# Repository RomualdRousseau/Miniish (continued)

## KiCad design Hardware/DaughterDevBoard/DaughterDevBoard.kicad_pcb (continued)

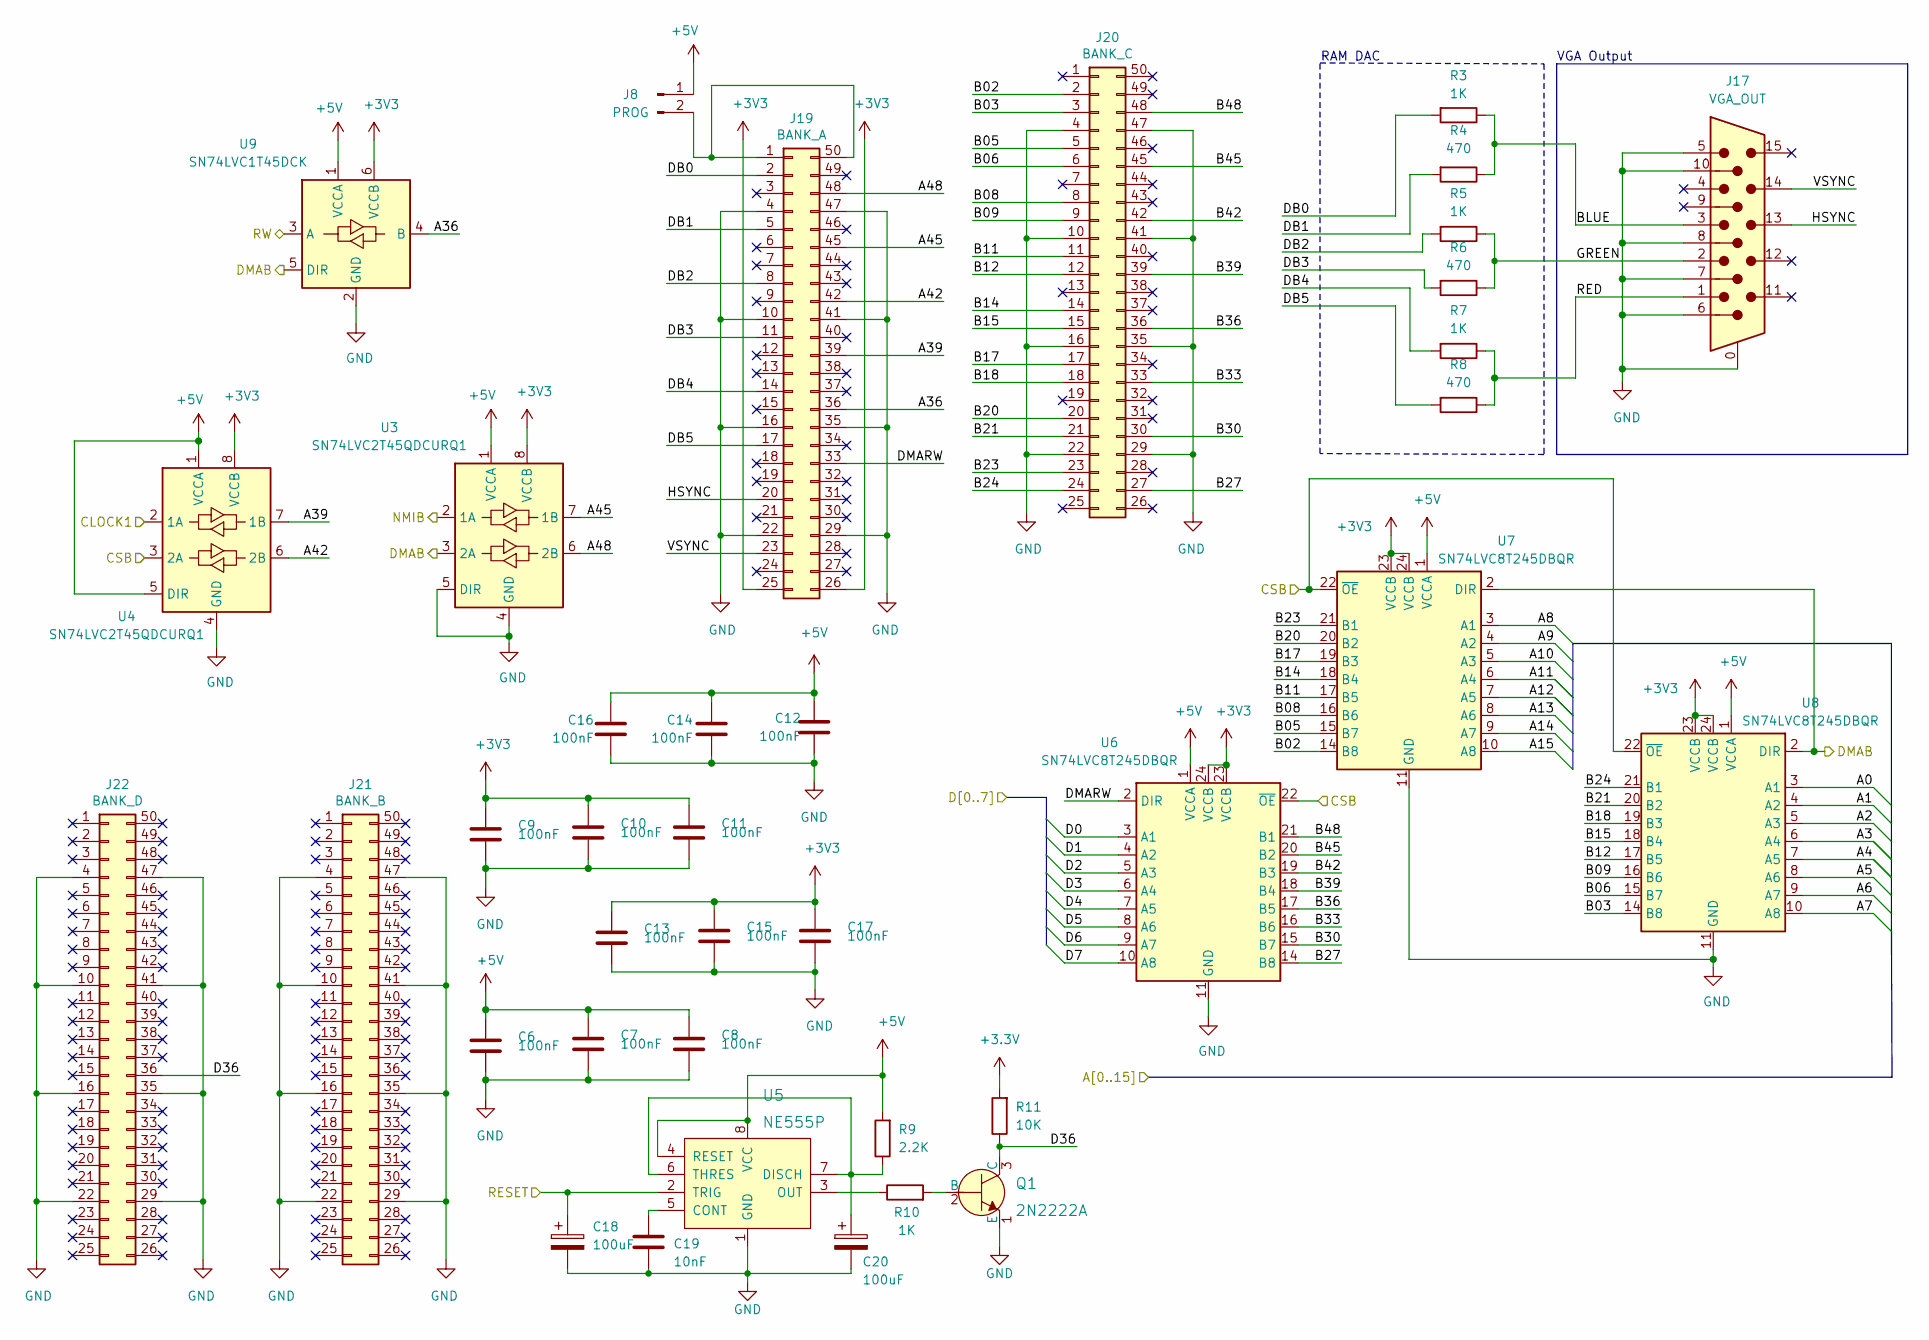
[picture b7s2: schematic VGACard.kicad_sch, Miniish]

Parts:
C6, C7, C8, C9, C10, C11, C12, C13, C14, C15, C16, C17: 100nF; C_0603_1608Metric
C18, C20: 100uF; CP_Radial_D5.0mm_P2.50mm
C19: 10nF; C_Disc_D5.0mm_W2.5mm_P2.50mm
J8: PROG; PinHeader_1x02_P2.54mm_Vertical
J17: VGA_OUT; DSUB-15-HD_Female_Horizontal_P2.29x1.98mm_EdgePinOffset8.35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
J19: BANK_A; 4UCON_2x25_P0.50mm_Vertical
J20: BANK_C; 4UCON_2x25_P0.50mm_Vertical
J21: BANK_B; 4UCON_2x25_P0.50mm_Vertical
J22: BANK_D; 4UCON_2x25_P0.50mm_Vertical
Q1: 2N2222A; TO-18-3; MPN 2N2222A; Digi-Key_PN 2N2222ACS-ND
R3, R5, R7, R10: 1K; R_Axial_DIN0207_L6.3mm_D2.5mm_P10.16mm_Horizontal
R4, R6, R8: 470; R_Axial_DIN0207_L6.3mm_D2.5mm_P10.16mm_Horizontal
R9: 2.2K; R_Axial_DIN0207_L6.3mm_D2.5mm_P10.16mm_Horizontal
R11: 10K; R_Axial_DIN0207_L6.3mm_D2.5mm_P10.16mm_Horizontal
U3, U4: SN74LVC2T45QDCURQ1; VSSOP-8_2.3x2mm_P0.5mm
U5: NE555P; DIP-8_W7.62mm; MPN NE555P; Digi-Key_PN 296-1411-5-ND
U6, U7, U8: SN74LVC8T245DBQR; TSSOP-24_4.4x7.8mm_P0.65mm
U9: SN74LVC1T45DCK; SOT-363_SC-70-6

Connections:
+5V: C6.1, C7.1, C8.1, C12.2, C14.2, C16.2, J8.1, R9.2, U3.1 (VCCA), U4.1 (VCCA), U4.5 (DIR), U5.4 (RESET), U5.8 (VCC), U6.1 (VCCA), U7.1 (VCCA), U8.1 (VCCA), U9.1 (VCCA); also elsewhere on the board
/AB0: U8.3 (A1); also elsewhere on the board
/AB1: U8.4 (A2); also elsewhere on the board
/AB2: U8.5 (A3); also elsewhere on the board
/AB3: U8.6 (A4); also elsewhere on the board
/AB4: U8.7 (A5); also elsewhere on the board
/AB5: U8.8 (A6); also elsewhere on the board
/AB6: U8.9 (A7); also elsewhere on the board
/AB7: U8.10 (A8); also elsewhere on the board
/AB8: U7.3 (A1); also elsewhere on the board
/AB9: U7.4 (A2); also elsewhere on the board
/AB10: U7.5 (A3); also elsewhere on the board
/AB11: U7.6 (A4); also elsewhere on the board
/AB12: U7.7 (A5); also elsewhere on the board
/AB13: U7.8 (A6); also elsewhere on the board
/AB14: U7.9 (A7); also elsewhere on the board
/AB15: U7.10 (A8); also elsewhere on the board
/DB0: U6.3 (A1); also elsewhere on the board
/DB1: U6.4 (A2); also elsewhere on the board
/DB2: U6.5 (A3); also elsewhere on the board
/DB3: U6.6 (A4); also elsewhere on the board
/DB4: U6.7 (A5); also elsewhere on the board
/DB5: U6.8 (A6); also elsewhere on the board
/DB6: U6.9 (A7); also elsewhere on the board
/DB7: U6.10 (A8); also elsewhere on the board
/VGA Card/A36: J19.36, U9.4 (B)
/VGA Card/A39: J19.39, U4.7 (1B)
/VGA Card/A42: J19.42, U4.6 (2B)
/VGA Card/A45: J19.45, U3.7 (1B)
/VGA Card/A48: J19.48, U3.6 (2B)
/VGA Card/B02: J20.2, U7.14 (B8)
/VGA Card/B03: J20.3, U8.14 (B8)
/VGA Card/B05: J20.5, U7.15 (B7)
/VGA Card/B06: J20.6, U8.15 (B7)
/VGA Card/B08: J20.8, U7.16 (B6)
/VGA Card/B09: J20.9, U8.16 (B6)
/VGA Card/B11: J20.11, U7.17 (B5)
/VGA Card/B12: J20.12, U8.17 (B5)
/VGA Card/B14: J20.14, U7.18 (B4)
/VGA Card/B15: J20.15, U8.18 (B4)
/VGA Card/B17: J20.17, U7.19 (B3)
/VGA Card/B18: J20.18, U8.19 (B3)
/VGA Card/B20: J20.20, U7.20 (B2)
/VGA Card/B21: J20.21, U8.20 (B2)
/VGA Card/B23: J20.23, U7.21 (B1)
/VGA Card/B24: J20.24, U8.21 (B1)
/VGA Card/B27: J20.27, U6.14 (B8)
/VGA Card/B30: J20.30, U6.15 (B7)
/VGA Card/B33: J20.33, U6.16 (B6)
/VGA Card/B36: J20.36, U6.17 (B5)
/VGA Card/B39: J20.39, U6.18 (B4)
/VGA Card/B42: J20.42, U6.19 (B3)
/VGA Card/B45: J20.45, U6.20 (B2)
/VGA Card/B48: J20.48, U6.21 (B1)
/VGA Card/BLUE: J17.3, R3.1, R4.1
/VGA Card/CLOCK1: U4.2 (1A); also elsewhere on the board
/VGA Card/CSB: U4.3 (2A), U6.22 (~OE), U7.22 (~OE), U8.22 (~OE); also elsewhere on the board
/VGA Card/D36: J22.36, Q1.3 (C), R11.1
/VGA Card/DB0: J19.2, R3.2
/VGA Card/DB1: J19.5, R4.2
/VGA Card/DB2: J19.8, R5.2
/VGA Card/DB3: J19.11, R6.2
/VGA Card/DB4: J19.14, R7.2
/VGA Card/DB5: J19.17, R8.2
/VGA Card/DMAB: U3.3 (2A), U7.2 (DIR), U8.2 (DIR), U9.5 (DIR); also elsewhere on the board
/VGA Card/DMARW: J19.33, U6.2 (DIR)
/VGA Card/GREEN: J17.2, R5.1, R6.1
/VGA Card/HSYNC: J17.13, J19.20
/VGA Card/NMIB: U3.2 (1A); also elsewhere on the board
/VGA Card/RED: J17.1, R7.1, R8.1
/VGA Card/RESET: C18.1, U5.2 (TRIG); also elsewhere on the board
/VGA Card/RW: U9.3 (A); also elsewhere on the board
/VGA Card/VSYNC: J17.14, J19.23
GND: C6.2, C7.2, C8.2, C9.2, C10.2, C11.2, C12.1, C13.2, C14.1, C15.2, C16.1, C17.2, C18.2, C19.2, C20.2, J17.0, J17.5, J17.6, J17.7, J17.8, J17.10, J19.4, J19.10, J19.16, J19.22, J19.29, J19.35, J19.41, J19.47, J20.4, J20.10, J20.16, J20.22, J20.29, J20.35, J20.41, J20.47, J21.4, J21.10, J21.16, J21.22, J21.29, J21.35, J21.41, J21.47, J22.4, J22.10, J22.16, J22.22, J22.29, J22.35, J22.41, J22.47, Q1.1 (E), U3.4 (GND), U3.5 (DIR), U4.4 (GND), U5.1 (GND), U6.11 (GND), U6.12 (GND), U6.13 (GND), U7.11 (GND), U7.12 (GND), U7.13 (GND), U8.11 (GND), U8.12 (GND), U8.13 (GND), U9.2 (GND); also elsewhere on the board
unnamed: C19.1, U5.5 (CONT)
unnamed: C20.1, R9.1, U5.6 (THRES), U5.7 (DISCH)
unnamed: J8.2, J19.1, J19.50
unnamed: Q1.2 (B), R10.2
unnamed: R10.1, U5.3 (OUT)

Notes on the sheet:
RAM DAC
VGA Output

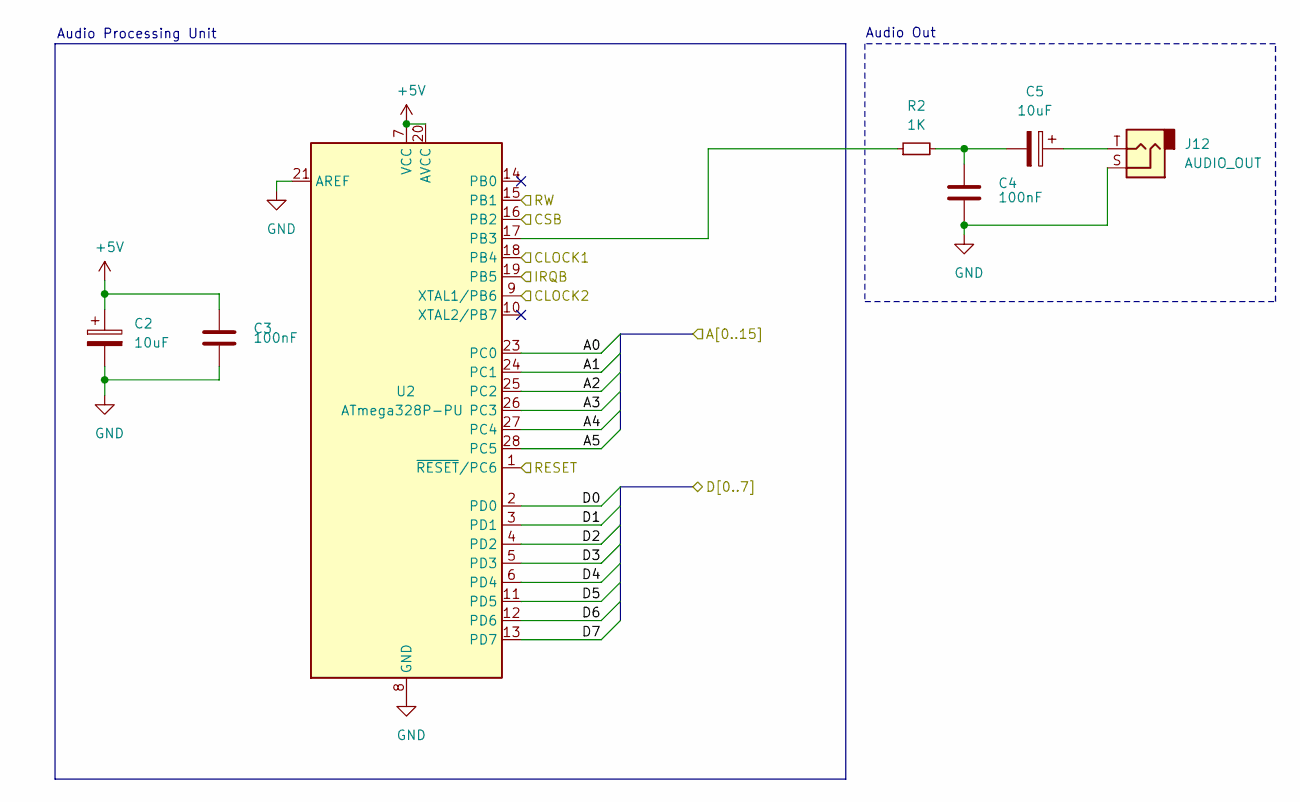
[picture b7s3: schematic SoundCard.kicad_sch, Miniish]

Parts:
C2, C5: 10uF; C_Radial_D5.0mm_H11.0mm_P2.00mm
C3, C4: 100nF; C_Disc_D5.0mm_W2.5mm_P2.50mm
J12: AUDIO_OUT; Jack_3.5mm_CUI_SJ1-3533NG_Horizontal
R2: 1K; R_Axial_DIN0207_L6.3mm_D2.5mm_P10.16mm_Horizontal
U2: ATmega328P-PU; DIP-28_W7.62mm

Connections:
+5V: C2.1, C3.1, U2.7 (VCC), U2.20 (AVCC); also elsewhere on the board
/AA0: U2.23 (PC0); also elsewhere on the board
/AA1: U2.24 (PC1); also elsewhere on the board
/AA2: U2.25 (PC2); also elsewhere on the board
/AA3: U2.26 (PC3); also elsewhere on the board
/AA4: U2.27 (PC4); also elsewhere on the board
/AA5: U2.28 (PC5); also elsewhere on the board
/DA0: U2.2 (PD0); also elsewhere on the board
/DA1: U2.3 (PD1); also elsewhere on the board
/DA2: U2.4 (PD2); also elsewhere on the board
/DA3: U2.5 (PD3); also elsewhere on the board
/DA4: U2.6 (PD4); also elsewhere on the board
/DA5: U2.11 (PD5); also elsewhere on the board
/DA6: U2.12 (PD6); also elsewhere on the board
/DA7: U2.13 (PD7); also elsewhere on the board
/SoundCard/CLOCK1: U2.18 (PB4); also elsewhere on the board
/SoundCard/CSB: U2.16 (PB2); also elsewhere on the board
/SoundCard/IRQB: U2.19 (PB5); also elsewhere on the board
/SoundCard/RESET: U2.1 (~RESET/PC6); also elsewhere on the board
/SoundCard/RW: U2.15 (PB1); also elsewhere on the board
APU_CLOCK: U2.9 (XTAL1/PB6); also elsewhere on the board
GND: C2.2, C3.2, C4.2, J12.S, U2.8 (GND), U2.21 (AREF), U2.22 (GND); also elsewhere on the board
unnamed: C4.1, C5.2, R2.2
unnamed: C5.1, J12.T
unnamed: R2.1, U2.17 (PB3)

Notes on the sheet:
Audio Out
Audio Processing Unit

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
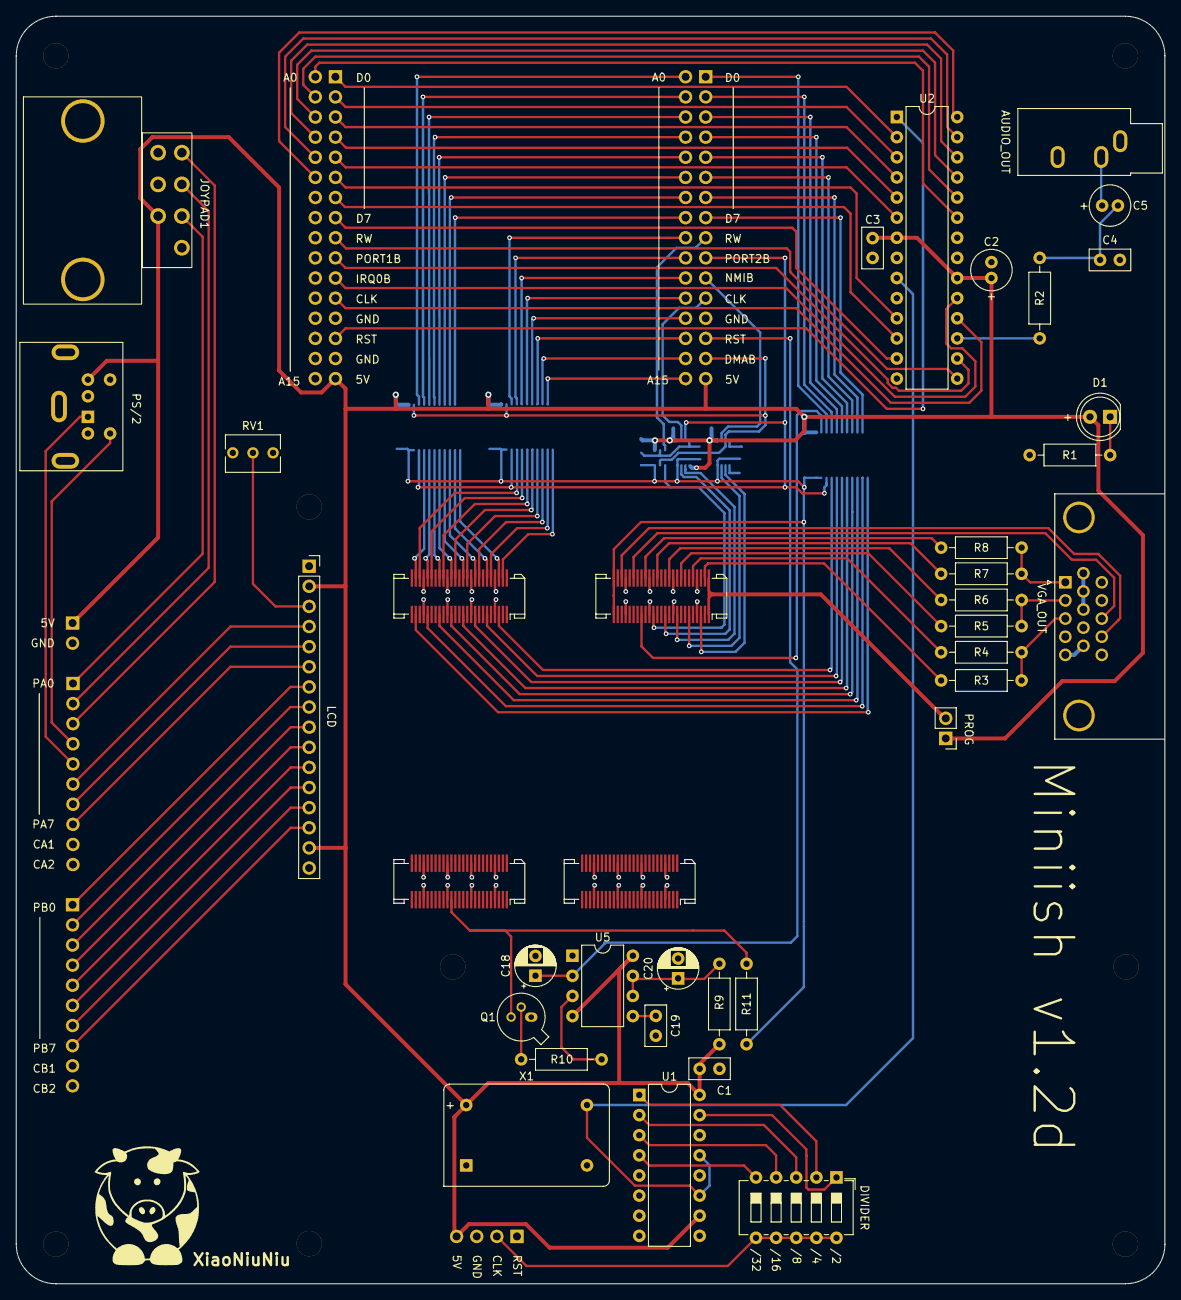
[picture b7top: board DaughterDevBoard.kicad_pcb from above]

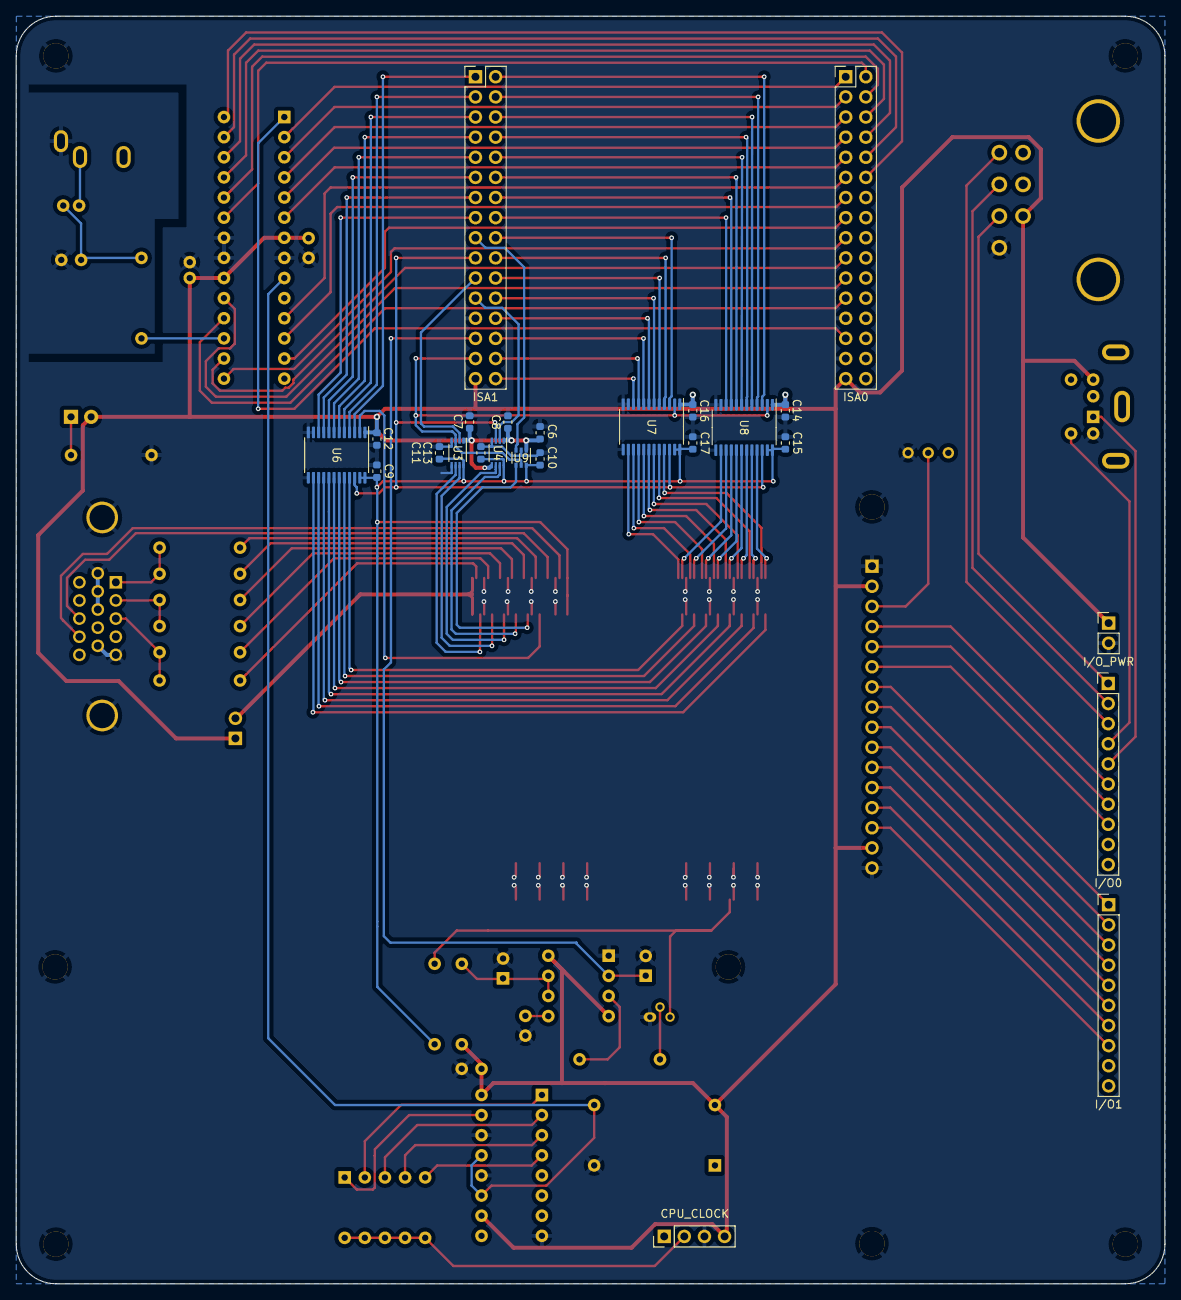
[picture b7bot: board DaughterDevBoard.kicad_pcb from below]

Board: 2 copper layers, 145.0 x 160.0 mm, 70 parts (24 on the bottom side), 127 nets.

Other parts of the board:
H7, H8: MountingHole_Pad
XiaoNiuNiu: LOGO; SmallCow

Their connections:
GND: H7.1, H8.1; also elsewhere on the board

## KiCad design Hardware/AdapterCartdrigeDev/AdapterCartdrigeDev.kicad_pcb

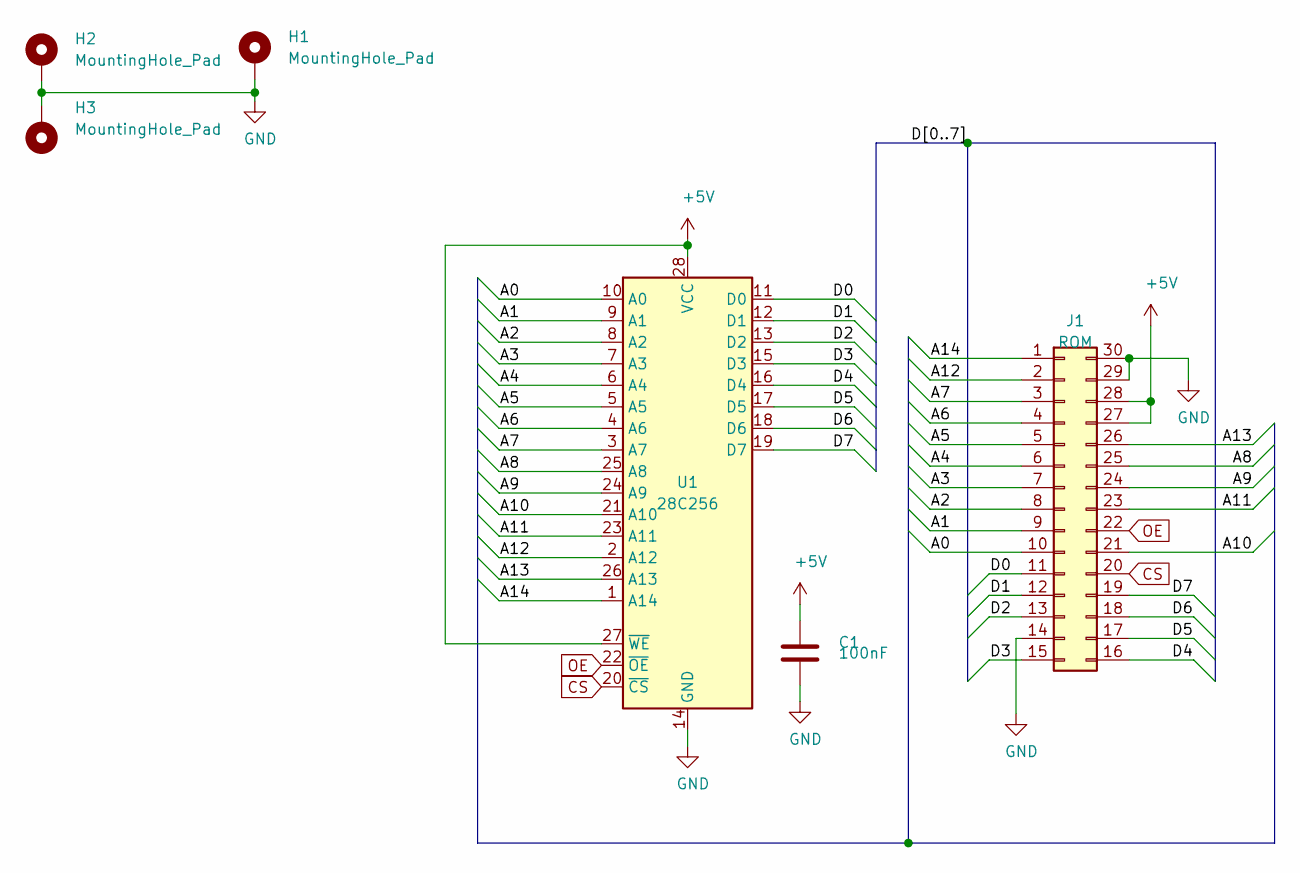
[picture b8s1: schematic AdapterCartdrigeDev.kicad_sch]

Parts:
C1: 100nF; C_Disc_D5.0mm_W2.5mm_P2.50mm
H1, H2, H3: MountingHole_Pad; MountingHole_3.2mm_M3
J1: ROM; PinHeader_2x15_P2.54mm_Vertical
U1: 28C256; DIP_Socket-28_W11.9_W12.7_W15.24_W17.78_W18.5_3M_228-1277-0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

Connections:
+5V: C1.1, J1.27, J1.28, U1.27 (~WE), U1.28 (VCC)
/A0: J1.10, U1.10 (A0)
/A1: J1.9, U1.9 (A1)
/A2: J1.8, U1.8 (A2)
/A3: J1.7, U1.7 (A3)
/A4: J1.6, U1.6 (A4)
/A5: J1.5, U1.5 (A5)
/A6: J1.4, U1.4 (A6)
/A7: J1.3, U1.3 (A7)
/A8: J1.25, U1.25 (A8)
/A9: J1.24, U1.24 (A9)
/A10: J1.21, U1.21 (A10)
/A11: J1.23, U1.23 (A11)
/A12: J1.2, U1.2 (A12)
/A13: J1.26, U1.26 (A13)
/A14: J1.1, U1.1 (A14)
/D0: J1.11, U1.11 (D0)
/D1: J1.12, U1.12 (D1)
/D2: J1.13, U1.13 (D2)
/D3: J1.15, U1.15 (D3)
/D4: J1.16, U1.16 (D4)
/D5: J1.17, U1.17 (D5)
/D6: J1.18, U1.18 (D6)
/D7: J1.19, U1.19 (D7)
CS: J1.20, U1.20 (~CS)
GND: C1.2, H1.1, H2.1, H3.1, J1.14, J1.29, J1.30, U1.14 (GND)
OE: J1.22, U1.22 (~OE)

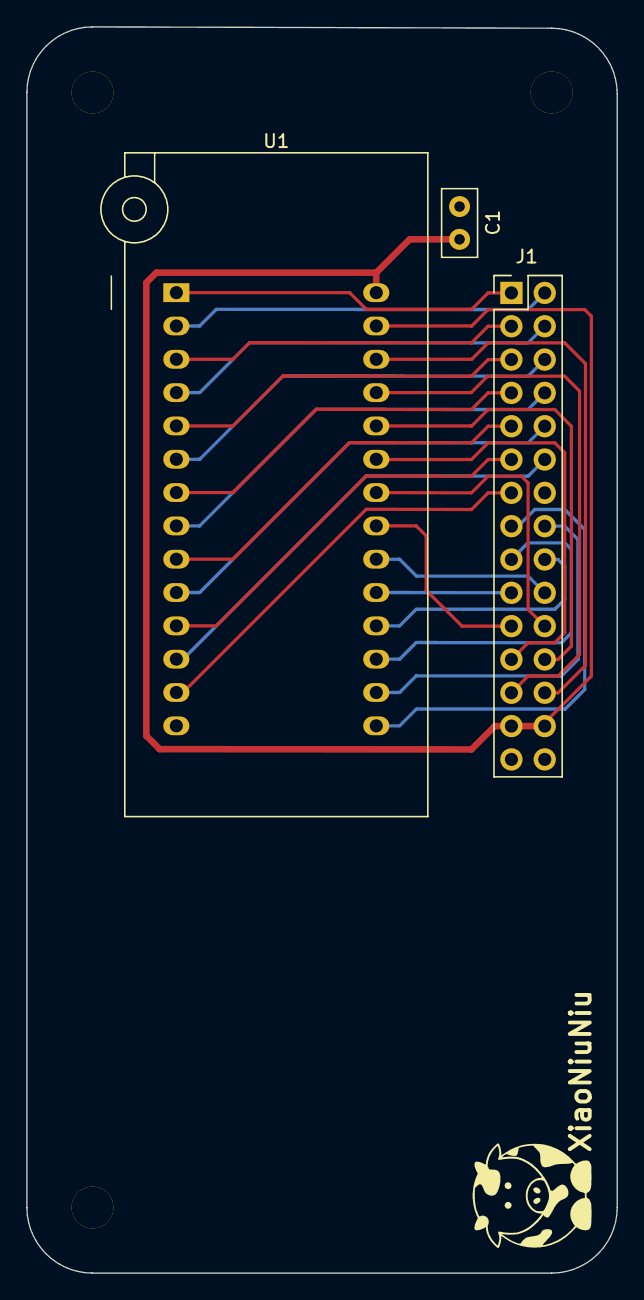
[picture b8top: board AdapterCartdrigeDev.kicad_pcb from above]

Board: 2 copper layers, 45.0 x 95.0 mm, 7 parts (0 on the bottom side), 27 nets.

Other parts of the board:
XiaoNiuNiu: LOGO; VerySmallCow

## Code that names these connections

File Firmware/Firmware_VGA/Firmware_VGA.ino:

/*
    Welcome to VGA v1.0 firmware

    To upload this firmware, select the following board:
    Board: "ATMEGA 328P"
    Clock: "20MHz"
    Bootloader: "Empty"
*/

#define CONTROL_PORT     PORTB
#define VADDR_PORT       PORTC
#define HADDR_PORT       PORTD

#define VADDR7_PIN       0  // PIN 8  (PB0)
#define CTRL_HSYNC_PIN   1  // PIN 9  (PB1)
#define CTRL_VSYNC_PIN   2  // PIN 10 (PB2)
#define CTRL_HLINE_PIN   3  // PIN 11 (PB3)
#define CTRL_VBLANK_PIN  4  // PIN 12 (PB4)

#define VSYNC_PULSE      27     // 86.4us rather larger than 64us
#define VSYNC_LENGTH     5209   // 16.668ms
#define VSYNC_START_LINE -76

#define HSYNC_PULSE      9      // 3.6us
#define HSYNC_LENGTH     79     // 31.6us

static volatile int vline = 0;

void setup() {
  
  // Initialize pins directions and values
  
  DDRB = 0b00001111;
  DDRC = 0b00000000;
  DDRD = 0b00000000;
  PORTB = 0;

  cli();

  // Clear and stop all timers

  TCCR0A = 0;
  TCCR0B = 0;

  TCCR1A = 0;
  TCCR1B = 0;
  
  TCCR2A = 0;
  TCCR2B = 0;

  // Setup Anti jitter on TIMER0

  TIMSK0=0;
  OCR0A=0;
  OCR0B=0;
  TCNT0=0;

  // Setup VSYNC pulse on TIMER1

  TCCR1A |= (1 << WGM11) | (1 << WGM10);   // Fast PWM
  TCCR1B |= (1 << WGM13) | (1 << WGM12);
  TIMSK1 |= (1 << OCIE1B) | (1 << OCIE1A); // Enable interrupts
  OCR1A = VSYNC_LENGTH;
  OCR1B = VSYNC_PULSE;

  // Setup HSYNC pulse on TIMER2
  
  TCCR2A |= (1 << WGM21) | (1 << WGM20);   // Fast PWM
  TCCR2B |= (1 << WGM22);
  TIMSK2 |= (1 << OCIE2B) | (1 << OCIE2A); // Enable interrupts
  OCR2A = HSYNC_LENGTH;
  OCR2B = HSYNC_PULSE;
  
  sei();

  // Start all timers

  TCCR0B |= (1 << CS00); // Prescaler 1/1
  TCCR1B |= (1 << CS11) | (1 << CS10); // Prescaler 1/64
  TCCR2B |= (1 << CS21); // Prescaler 1/8
}

// VSync Interrupts

ISR (TIMER1_COMPA_vect)
{ 
  asm volatile("sbi %[portb], %[outp]\n"::[portb] "I" (_SFR_IO_ADDR(CONTROL_PORT)), [outp] "i" (CTRL_VSYNC_PIN):);
}

ISR (TIMER1_COMPB_vect)
{   
  asm volatile("cbi %[portb], %[outp]\n"::[portb] "I" (_SFR_IO_ADDR(CONTROL_PORT)), [outp] "i" (CTRL_VSYNC_PIN):);
  vline = VSYNC_START_LINE;
  TCNT0 = 0;
}

// HSync Interrupts

ISR (TIMER2_COMPA_vect)
{ 
  asm volatile("cbi %[portb], %[outp]\n"::[portb] "I" (_SFR_IO_ADDR(CONTROL_PORT)), [outp] "i" (CTRL_HSYNC_PIN):);
}

ISR (TIMER2_COMPB_vect)
{
  asm volatile("sbi %[portb], %[outp]\n"::[portb] "I" (_SFR_IO_ADDR(CONTROL_PORT)), [outp] "i" (CTRL_HSYNC_PIN):);
  vline++;

  //
  // Back Porch Section
  //
  
  if (((unsigned) vline) >= 389) {
    if (vline == 389) {
      // Disable data outputs
      DDRB = 0b00011110;
      DDRC = 0b00000000;
      DDRD = 0b00000000;
      // Notify VBLANK start
      PORTB |= (1 << CTRL_VBLANK_PIN);
    } else if (vline == -5) {
      // Notify VBLANK stop
      PORTB &= ~(1 << CTRL_VBLANK_PIN);
    } else if (vline == -1) {
      // Enable data outputs
      DDRB = 0b00011111;
      DDRC = 0b00111111;
      DDRD = 0b11111111;
    }
    return;
  }


  // Initialize line address counter 
  
  asm volatile(
    //PORTB = HIGH(vline >> 2);
    "    sbrc %[vline], 6\n"
    "    sbi %[portb], %[outp]\n"
    "    sbrs %[vline], 6\n"
    "    cbi %[portb], %[outp]\n" 
    //PORTC = LOW(vline >> 2);
    "    andi %[vline], 0x3F\n"
    "    out %[portc], %[vline]\n"
    //PORTD = 0;
    "    out %[portd], __zero_reg__\n"
    :
    :[portb] "I" (_SFR_IO_ADDR(CONTROL_PORT)),
     [portc] "I" (_SFR_IO_ADDR(VADDR_PORT)),
     [portd] "I" (_SFR_IO_ADDR(HADDR_PORT)),
     [outp] "i" (VADDR7_PIN),
     [vline] "r" (vline >> 2)
    :"r20"
  );

  // Sync and stabilize signal

  #define DEJITTER_OFFSET 2
  #define DEJITTER_SYNC   -2
  asm volatile(
    "     lds r16, %[timer]\n"
    "     add r16, %[toff]\n"
    "     subi r16, %[tsync]\n"
    "     andi r16, 3\n"
    "     call TLH\n"
    "TLH:\n"
    "     pop r31\n"
    "     pop r30\n"
    "     adiw r30, (LWH-TLH-2)\n"
    "     add r30, r16\n"
    "     ijmp\n"
    "LWH:\n"
    ".rept 8\n"
    "     nop\n"
    ".endr\n"
    :
    : [timer] "i" (&TCNT0),
      [toff] "i" ((uint8_t) DEJITTER_OFFSET),
      [tsync] "i" ((uint8_t) DEJITTER_SYNC)
    : "r30", "r31", "r16", "r17"
  );

  //
  // Visible Section
  //

  // Notify HLINE start

  asm volatile("cbi %[portb], %[outp]\n"::[portb] "I" (_SFR_IO_ADDR(CONTROL_PORT)), [outp] "i" (CTRL_HLINE_PIN):);

  // Output pixels by incrementing the line address counter
  
  asm volatile(
      "    ldi r20, 0\n"
      ".rept 159\n"
      "    inc r20\n"
      "    out %[portd], r20\n"
      "    nop\n"
      ".endr\n"
      :
      :[portd] "I" (_SFR_IO_ADDR(HADDR_PORT))
      :"r20"
    );
    
  // Notify HLINE stop
  
  asm volatile("sbi %[portb], %[outp]\n"::[portb] "I" (_SFR_IO_ADDR(CONTROL_PORT)), [outp] "i" (CTRL_HLINE_PIN):);
  
  //
  // Front Porch Section
  //

  asm volatile(
      ".rept 4\n"
      "    nop\n"
      ".endr\n"
    );
}

void loop() {
  // Do nothing
}

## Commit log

2020-11-21 Add buffers to extenstion ports
2020-11-21 Document
2020-11-21 Cleanup
2020-11-22 Complete buffred extension ports
2020-12-05 Replace logic IC 4xxx by 74hcxx
2020-12-25 Finalize daughter board
2020-12-31 implement graphic loading from ROM
2021-01-01 Fix PPU dma loader
2021-01-02 Fix PPU
2021-01-02 Clean up
2021-01-03 Implement APU and fix schematics
2021-01-09 Implement DMA and PCB ports
2021-01-31 Version 1.2
2021-04-26 New PLD logic, VGA, DMA ...
2021-12-21 Ignore Kicad backups
2022-05-03 New PPU - Direct Video Pixel
2022-05-09 Fix clock edge detection and refacter VGA signals
2022-05-10 Add DMA transfer
2022-05-21 Fix Reset, WAI Signal, Add PROG jumper and reformat luc files
2022-05-21 Cleanup and update version
2022-05-21 Decouple ramdac and picture processing
2022-05-22 Add map management and scrolling
2022-05-28 Add OAM and Miniish editor
2022-05-28 Add sprite
2022-05-28 Better example with animation
2022-05-30 Increase to 64 sprites per frame
2022-05-31 Refactor, add ctrl and status, fix sprite at boundaries
2022-06-01 Add status read and map vram access
2022-06-02 Add APU
2022-06-04 Add music editor
2022-06-04 Add multi-channel
2022-06-04 Remove pycache
2022-06-04 Refactor
2022-06-04 Transfer audio data to asm
2022-06-05 Fix synthetiser
2022-06-07 Fix APU
2022-06-07 Add monostable to reset PPU
2022-06-10 Generates automatically APU tables from pyco synth
2022-06-10 Add volume and fix enveloppes
2022-06-11 Enhance noise oscillator
2022-06-12 Better console support
2022-06-17 Remove Alchitry shield
2022-06-18 Add asm library
2022-06-19 Build a library to link with sketch
2022-06-20 Fix PPU read map
2022-06-20 Add sound sfx
2022-07-05 Start implementation repeat commands
2023-05-06 New motherboard version
2023-05-19 Finalize 1.3
2023-05-31 Version 1.3
2023-06-04 Add SPI test
2023-06-05 Add SPI Board
2023-07-15 A lot of new hardware
2023-07-16 Serial Software
2023-07-23 Implement my wozmon
2023-07-23 Better output
2023-08-27 Add horizontal scrolling
2023-08-27 Add a mini term
2023-09-02 soncole implements like a terminal
2023-09-03 Fix for poetry
2023-09-10 Big refactor
2023-09-11 serial as kernel
2023-09-16 Implemen tupload sketch
2023-09-16 add commands
2023-09-17 Better disk driver
2023-11-05 Improve scheduler
2023-11-11 Refactor scheduler
2023-11-12 Add arduino firmware
2023-11-13 Setup tasks and properties
2023-11-16 New hardware
2023-11-28 Add nfr24l01 protocol
2023-11-28 Fix makefile clean and tab config
2023-11-28 Clean libs as well
2023-11-28 Init channels and map values
2023-11-29 Set pins
2023-12-02 Rewrite nrf27 mini lib
2024-11-30 Add ArduinoMultiInterface
2024-12-07 Better poetry handling
2024-12-07 Fix Python
2025-11-04 feat: modify mother board for paging and dma
2026-05-26 chore: cleanup and add justfile
